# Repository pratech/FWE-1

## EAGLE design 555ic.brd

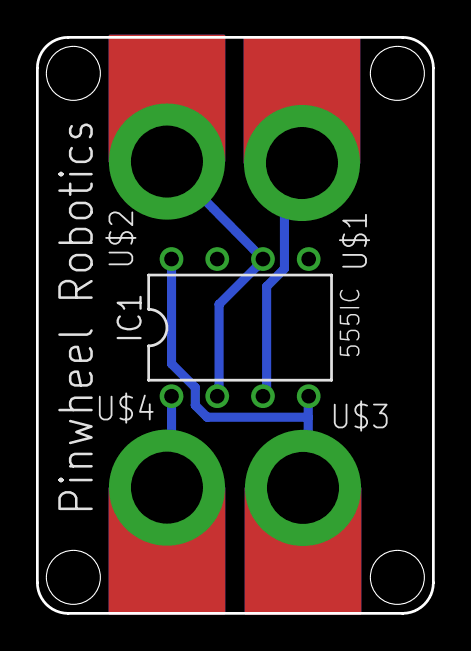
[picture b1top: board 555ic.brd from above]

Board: 2 copper layers, 22.0 x 32.0 mm, 5 parts (0 on the bottom side), 4 nets.

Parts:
IC1: LM555N; DIL08
U$1, U$2, U$3, U$4: MICROBIT_PAD

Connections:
5V: IC1.4, IC1.8, U$3.PAD
GND: IC1.1, U$4.PAD
unnamed: IC1.3, U$1.PAD
unnamed: IC1.2, IC1.6, U$2.PAD

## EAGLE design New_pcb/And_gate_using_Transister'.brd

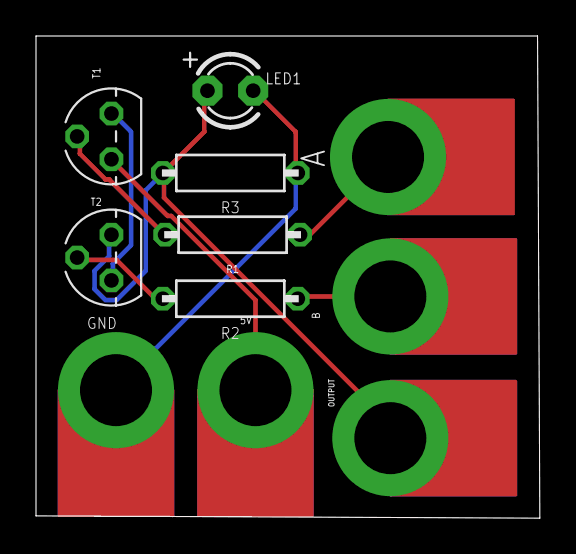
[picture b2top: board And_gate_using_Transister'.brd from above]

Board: 2 copper layers, 28.0 x 26.8 mm, 11 parts (0 on the bottom side), 8 nets.

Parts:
5V: MICROBIT_PAD
A: MICROBIT_PAD
B: MICROBIT_PAD
GND: MICROBIT_PAD
LED1: LED3MM
OUTPUT: MICROBIT_PAD
R1, R2, R3: R0207/7
T1, T2: BC547; TO92

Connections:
5V: 5V.PAD, T1.3
GND: GND.PAD, LED1.K, R3.1
unnamed: R2.2, T2.2
unnamed: T1.1, T2.3
unnamed: LED1.A, OUTPUT.PAD, R3.2, T2.1
unnamed: R1.2, T1.2
unnamed: A.PAD, R1.1
unnamed: B.PAD, R2.1

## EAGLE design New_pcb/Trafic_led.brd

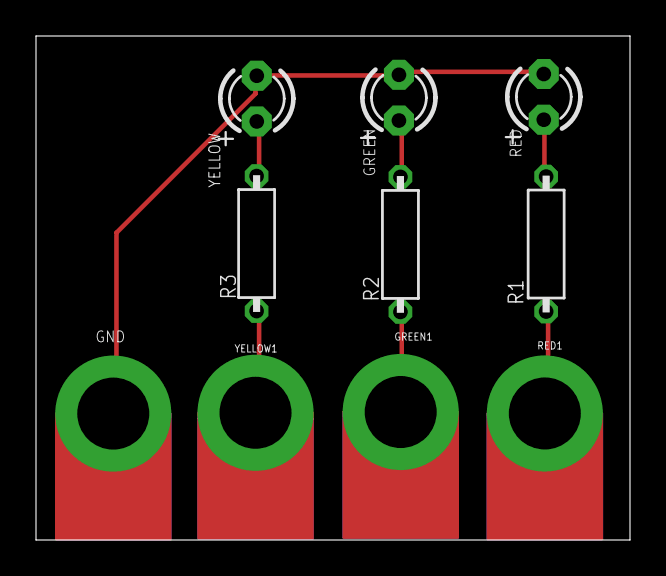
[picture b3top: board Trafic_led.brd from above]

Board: 2 copper layers, 33.0 x 28.0 mm, 10 parts (0 on the bottom side), 7 nets.

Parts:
GND: MICROBIT_PAD
GREEN: LED3MM
GREEN1: MICROBIT_PAD
R1, R2, R3: 330; R0207/7
RED: LED3MM
RED1: MICROBIT_PAD
YELLOW: LED3MM
YELLOW1: MICROBIT_PAD

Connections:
GND: GND.PAD, GREEN.K, RED.K, YELLOW.K
unnamed: R1.1, RED1.PAD
unnamed: R3.1, YELLOW1.PAD
unnamed: GREEN.A, R2.2
unnamed: GREEN1.PAD, R2.1
unnamed: R3.2, YELLOW.A
unnamed: R1.2, RED.A

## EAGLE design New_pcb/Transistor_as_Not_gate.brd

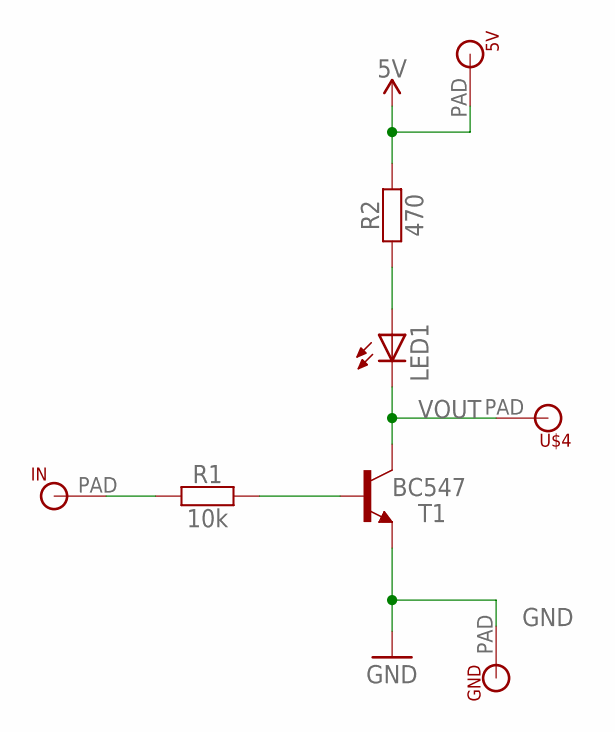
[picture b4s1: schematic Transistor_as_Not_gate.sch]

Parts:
5V: MICROBIT_PAD
GND: MICROBIT_PAD
IN: MICROBIT_PAD
LED1: LED3MM
R1: 10k; R0207/7
R2: 470; R0207/7
T1: BC547; TO92
U$4: MICROBIT_PAD

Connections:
5V: 5V.PAD, R2.2
GND: GND.PAD, T1.1 (E)
unnamed: R1.2, T1.2 (B)
unnamed: LED1.A, R2.1
unnamed: IN.PAD, R1.1
VOUT: LED1.K (C), T1.3 (C), U$4.PAD

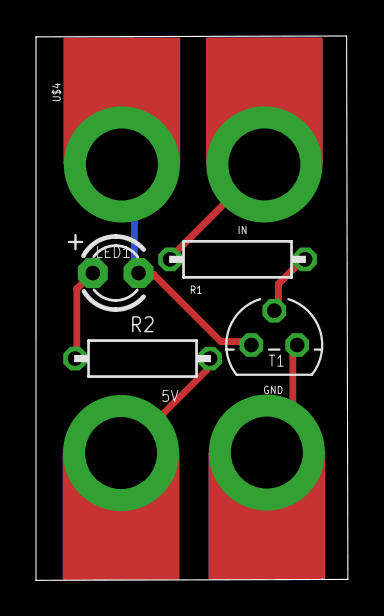
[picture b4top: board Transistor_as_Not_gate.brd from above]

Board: 2 copper layers, 17.3 x 30.2 mm, 8 parts (0 on the bottom side), 6 nets.

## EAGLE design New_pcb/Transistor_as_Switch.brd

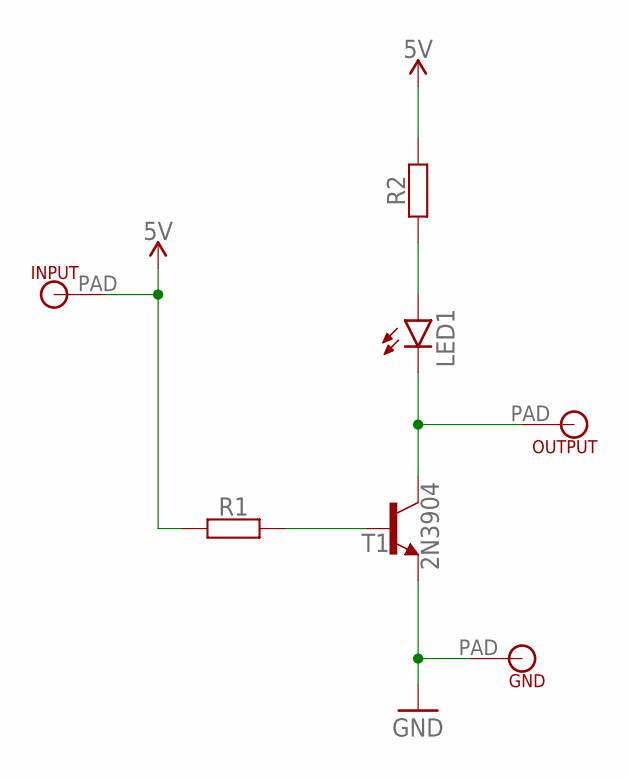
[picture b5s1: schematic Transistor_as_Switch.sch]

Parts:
GND: MICROBIT_PAD
INPUT: MICROBIT_PAD
LED1: LEDCHIP-LED0805; CHIP-LED0805
OUTPUT: MICROBIT_PAD
R1, R2: RESISTOR-10; R0207/10
T1: 2N3904; TO92

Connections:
5V: INPUT.PAD, R1.1, R2.2
GND: GND.PAD, T1.3 (E)
unnamed: LED1.A, R2.1
unnamed: LED1.C, OUTPUT.PAD, T1.1 (C)
unnamed: R1.2, T1.2 (B)

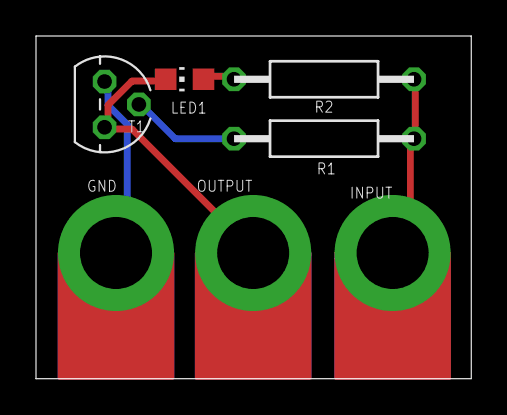
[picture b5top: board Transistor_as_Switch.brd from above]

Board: 2 copper layers, 24.2 x 19.0 mm, 7 parts (0 on the bottom side), 5 nets.

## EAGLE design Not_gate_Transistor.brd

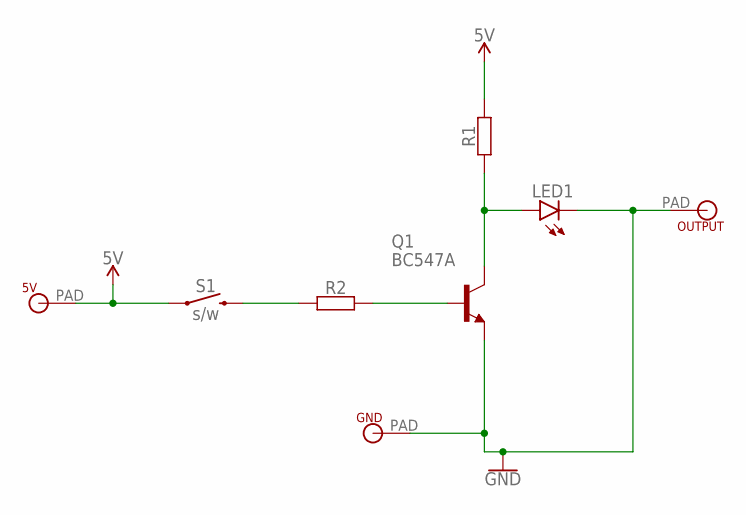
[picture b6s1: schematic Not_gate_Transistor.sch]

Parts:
5V: 5V; MICROBIT_PAD
GND: MICROBIT_PAD
LED1: LEDCHIP-LED0805; CHIP-LED0805
OUTPUT: MICROBIT_PAD
Q1: BC547A; TO92
R1, R2: RESISTOR-07; R0207/7
S1: s/w; TACTILE_SWITCH_PTH_6.0MM

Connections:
5V: 5V.PAD, R1.2, S1.1
GND: GND.PAD, LED1.C, OUTPUT.PAD, Q1.1 (E)
unnamed: LED1.A, Q1.3 (C), R1.1
unnamed: Q1.2 (B), R2.2
unnamed: R2.1, S1.3 (2)

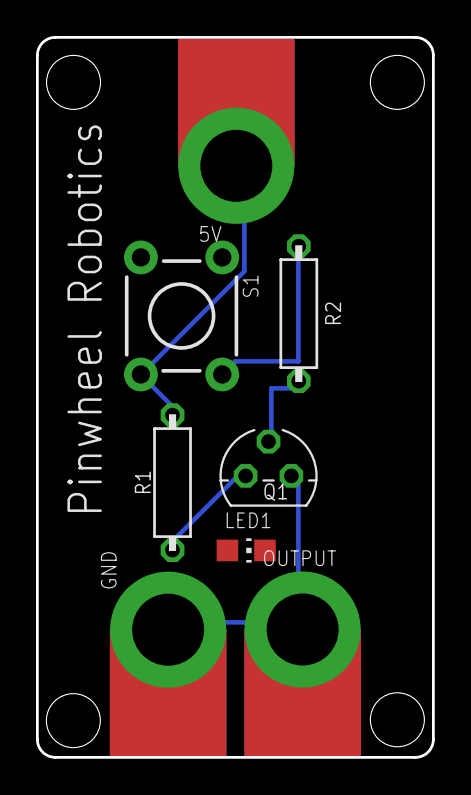
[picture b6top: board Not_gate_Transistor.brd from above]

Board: 2 copper layers, 22.0 x 40.0 mm, 8 parts (0 on the bottom side), 5 nets.

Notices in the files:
parts and their libraries:
SparkFun-PowerSymbols: Licensing: Creative Commons ShareAlike 4.0 International - https://creativecommons.org/licenses/by-sa/4.0
